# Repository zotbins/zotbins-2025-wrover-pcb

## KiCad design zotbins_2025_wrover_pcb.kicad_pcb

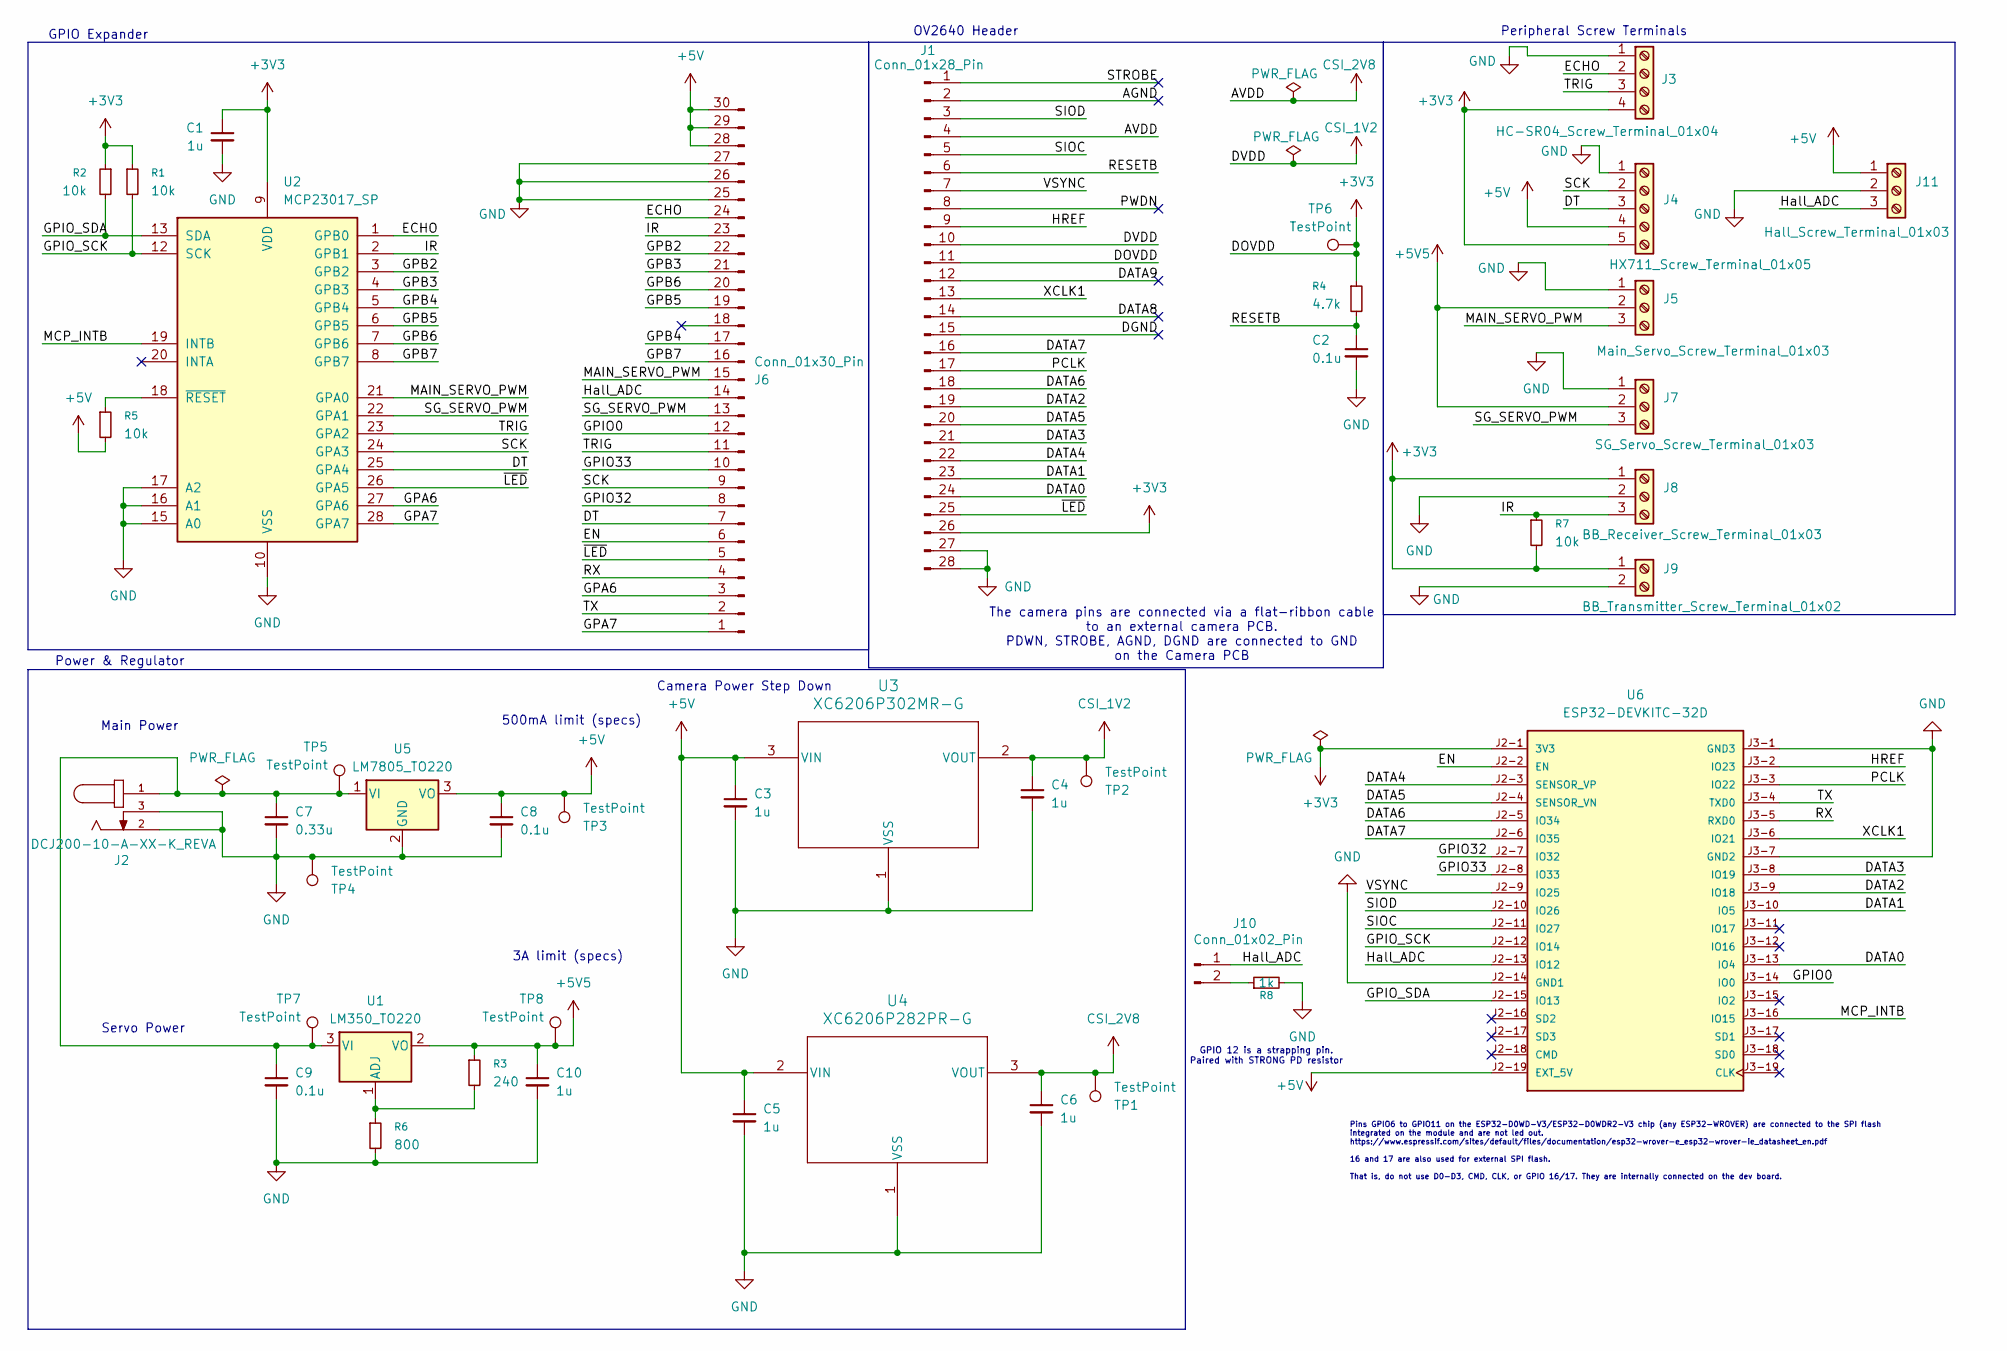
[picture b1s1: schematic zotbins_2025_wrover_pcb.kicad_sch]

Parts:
C1, C3, C4, C5, C6, C10: 1u; C_Disc_D4.3mm_W1.9mm_P5.00mm
C2, C8, C9: 0.1u; C_Disc_D4.3mm_W1.9mm_P5.00mm
C7: 0.33u; C_Disc_D4.3mm_W1.9mm_P5.00mm
J1: Conn_01x28_Pin; TE_2-84953-8_1x28-1MP_P1.0mm_Horizontal
J2: DCJ200-10-A-XX-K_REVA; GCT_DCJ200-10-A-XX-K_REVA; PARTREV A
J3: HC-SR04_Screw_Terminal_01x04; TerminalBlock_4Ucon_1x04_P3.50mm_Vertical
J4: HX711_Screw_Terminal_01x05; TerminalBlock_4Ucon_1x05_P3.50mm_Vertical
J5: Main_Servo_Screw_Terminal_01x03; TerminalBlock_4Ucon_1x03_P3.50mm_Vertical
J6: Conn_01x30_Pin; PinSocket_2x15_P2.54mm_Vertical
J7: SG_Servo_Screw_Terminal_01x03; TerminalBlock_4Ucon_1x03_P3.50mm_Vertical
J8: BB_Receiver_Screw_Terminal_01x03; TerminalBlock_4Ucon_1x03_P3.50mm_Vertical
J9: BB_Transmitter_Screw_Terminal_01x02; TerminalBlock_4Ucon_1x02_P3.50mm_Vertical
J10: Conn_01x02_Pin; PinSocket_1x02_P2.54mm_Vertical
J11: Hall_Screw_Terminal_01x03; TerminalBlock_4Ucon_1x03_P3.50mm_Vertical
R1, R2, R5, R7: 10k; R_Axial_DIN0207_L6.3mm_D2.5mm_P10.16mm_Horizontal
R3: 240; R_Axial_DIN0207_L6.3mm_D2.5mm_P10.16mm_Horizontal
R4: 4.7k; R_Axial_DIN0207_L6.3mm_D2.5mm_P10.16mm_Horizontal
R6: 800; R_Axial_DIN0207_L6.3mm_D2.5mm_P10.16mm_Horizontal
R8: 1k; R_Axial_DIN0207_L6.3mm_D2.5mm_P10.16mm_Horizontal
TP1, TP2, TP3, TP4, TP5, TP6, TP7, TP8: TestPoint; TestPoint_Keystone_5005-5009_Compact
U1: LM350_TO220; TO-220-3_Vertical
U2: MCP23017_SP; DIP-28_W7.62mm
U3: XC6206P302MR-G; SOT-23_TOR
U4: XC6206P282PR-G; SOT-89_TOR
U5: LM7805_TO220; TO-220-3_Vertical
U6: ESP32-DEVKITC-32D; MODULE_ESP32-DEVKITC-32D; PARTREV V4

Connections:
+3V3: C1.1, J1.11, J1.26, J3.4, J4.5, J8.1, J9.1, R1.1, R2.1, R4.1, R7.2, TP6.1, U2.9 (VDD), U6.J2-1 (3V3)
+5V: C3.1, C5.1, C8.1, J4.4, J6.28, J6.29, J6.30, J11.1, R5.2, TP3.1, U3.3 (VIN), U4.2 (VIN), U5.3 (VO), U6.J2-19 (EXT_5V)
+5V5: C10.1, J5.2, J7.2, R3.1, TP8.1, U1.2 (VO)
/AGND: J1.2
/DATA0: J1.24, U6.J3-13 (IO4)
/DATA1: J1.23, U6.J3-10 (IO5)
/DATA2: J1.19, U6.J3-9 (IO18)
/DATA3: J1.21, U6.J3-8 (IO19)
/DATA4: J1.22, U6.J2-3 (SENSOR_VP)
/DATA5: J1.20, U6.J2-4 (SENSOR_VN)
/DATA6: J1.18, U6.J2-5 (IO34)
/DATA7: J1.16, U6.J2-6 (IO35)
/DATA8: J1.14
/DATA9: J1.12
/DGND: J1.15
/DT: J4.3, J6.7, U2.25 (GPA4)
/ECHO: J3.2, J6.24, U2.1 (GPB0)
/EN: J6.6, U6.J2-2 (EN)
/GPA6: J6.3, U2.27 (GPA6)
/GPA7: J6.1, U2.28 (GPA7)
/GPB2: J6.22, U2.3 (GPB2)
/GPB3: J6.21, U2.4 (GPB3)
/GPB4: J6.17, U2.5 (GPB4)
/GPB5: J6.19, U2.6 (GPB5)
/GPB6: J6.20, U2.7 (GPB6)
/GPB7: J6.16, U2.8 (GPB7)
/GPIO0: J6.12, U6.J3-14 (IO0)
/GPIO32: J6.8, U6.J2-7 (IO32)
/GPIO33: J6.10, U6.J2-8 (IO33)
/GPIO_SCK: R1.2, U2.12 (SCK), U6.J2-12 (IO14)
/GPIO_SDA: R2.2, U2.13 (SDA), U6.J2-15 (IO13)
/HREF: J1.9, U6.J3-2 (IO23)
/Hall_ADC: J6.14, J10.1, J11.3, U6.J2-13 (IO12)
/IR: J6.23, J8.3, R7.1, U2.2 (GPB1)
/MAIN_SERVO_PWM: J5.3, J6.15, U2.21 (GPA0)
/MCP_INTB: U2.19 (INTB), U6.J3-16 (IO15)
/PCLK: J1.17, U6.J3-3 (IO22)
/PWDN: J1.8
/RESETB: C2.1, J1.6, R4.2
/RX: J6.4, U6.J3-5 (RXD0)
/SCK: J4.2, J6.9, U2.24 (GPA3)
/SG_SERVO_PWM: J6.13, J7.3, U2.22 (GPA1)
/SIOC: J1.5, U6.J2-11 (IO27)
/SIOD: J1.3, U6.J2-10 (IO26)
/STROBE: J1.1
/TRIG: J3.3, J6.11, U2.23 (GPA2)
/TX: J6.2, U6.J3-4 (TXD0)
/VSYNC: J1.7, U6.J2-9 (IO25)
/XCLK1: J1.13, U6.J3-6 (IO21)
/~LED: J1.25, J6.5, U2.26 (GPA5)
CSI_1V2: C4.1, J1.10, TP2.1, U3.2 (VOUT)
CSI_2V8: C6.1, J1.4, TP1.1, U4.3 (VOUT)
GND: C1.2, C2.2, C3.2, C4.2, C5.2, C6.2, C7.2, C8.2, C9.2, C10.2, J1.27, J1.28, J2.2, J2.3, J3.1, J4.1, J5.1, J6.25, J6.26, J6.27, J7.1, J8.2, J9.2, J11.2, R6.2, R8.2, TP4.1, U2.10 (VSS), U2.15 (A0), U2.16 (A1), U2.17 (A2), U3.1 (VSS), U4.1 (VSS), U5.2 (GND), U6.J2-14 (GND1), U6.J3-1 (GND3), U6.J3-7 (GND2)
unnamed: J10.2, R8.1
unnamed: R3.2, R6.1, U1.1 (ADJ)
unnamed: C7.1, C9.1, J2.1, TP5.1, TP7.1, U1.3 (VI), U5.1 (VI)
unnamed: R5.1, U2.18 (~RESET)

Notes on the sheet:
Power & Regulator
Main Power
GPIO 12 is a strapping pin. Paired with STRONG PD resistor
500mA limit (specs)
GPIO Expander
The camera pins are connected via a flat-ribbon cable to an external camera PCB. PDWN, STROBE, AGND, DGND are connected to GND on the Camera PCB
Camera Power Step Down
Servo Power
3A limit (specs)
Peripheral Screw Terminals
Pins GPIO6 to GPIO11 on the ESP32-D0WD-V3/ESP32-D0WDR2-V3 chip (any ESP32-WROVER) are connected to the SPI flash integrated on the module and are not led out. https://www.espressif.com/sites/default/files/documentation/esp32-wrover-e_esp32-wrover-ie_datasheet_en.pdf 16 and 17 are also used for exte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
OV2640 Header

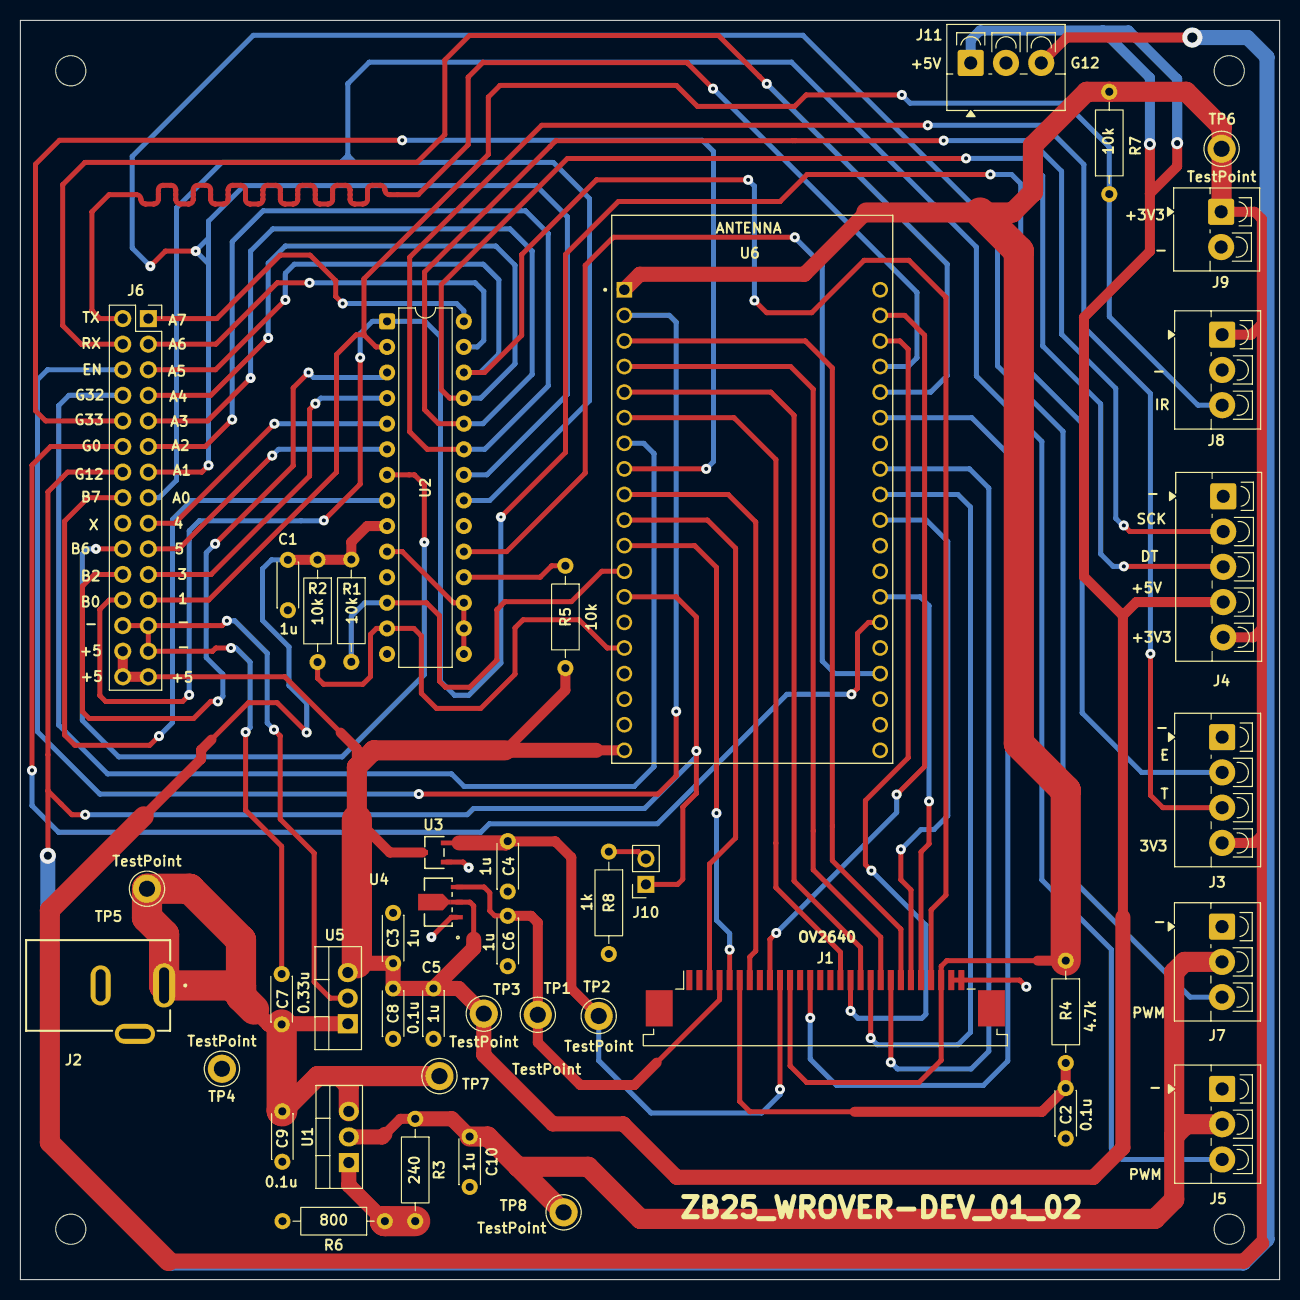
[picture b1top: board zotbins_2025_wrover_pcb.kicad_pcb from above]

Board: 2 copper layers, 125.0 x 125.0 mm, 43 parts (0 on the bottom side), 51 nets.

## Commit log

2025-10-08 init
2025-10-11 Camera and GPIO Expander sch updated
2025-10-11 All necessary hardware tests completed
2025-10-11 pins reconfigured
2025-10-14 added footprints
2025-10-20 resolved ERC checks, footprint incompatibilities, symbol library not found errors; 3 ERC violations surpressed intentionally
2025-10-20 configured power section ratsnest
2025-10-20 sorted ratsnest
2025-10-20 completed power traces; currently ignoring DRC violations from ov2640 smd module ( 90+ violations :( )
2025-10-21 partially completed gpio shield
2025-10-21 camera module connections left -- need to make constraints more marginal to account for tight smd constraints. (65 drc violations from footprint alone)
2025-10-23 current traces finished; todo: add servo + other peripheral terminal screws + adjust pcb size
2025-10-23 minor adjustments and size adjustment. Ready for final stage -- ALL PERIPHERALS. The current version is the most minimal version of a devboard.
2025-10-23 no changes
2025-10-27 basically the final version; just final adjustments with labeling and silkscreen needed. Traces, all components are all set.
2025-10-27 forgot to push changed pins on the schematic
2025-10-27 SCHEMATIC EDITS ONLY: remodified servo power to be unified under 1 barrel jack. Interrupt pins rerouted.
2025-10-27 complete
2025-10-27 retuned tx track or somth
2025-10-28 prepare for order, Iteration 1 complete
2025-11-09 hx711 bug update -- Digikey vendor sells different version of hx711 -> updated schematic + footprint
2025-11-10 Schematic work only: added LED circuitry, bug fixes on GPIO expander (5V -> 3.3V).
2025-11-10 completed PCB changes for iteration 2
2025-11-10 minor adjustments + gerber files produced
2025-11-11 fixed GPIO issue within gpio expander
2025-11-13 iteration 2 modified, components changed
2025-11-14 changed hcsr04 power to 3V3 as this component changed models
2025-11-14 fixed net name ambiguity on schematic
2025-11-18 ordered version + gerber
